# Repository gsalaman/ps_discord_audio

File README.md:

# Playstion/Discord Audio Mixer Project
This project provides a box that mixes together Audio and Microphone from both Playstation and Discord sources into a single headset. 

Quick Links:
* [Project Proposal](https://docs.google.com/document/d/1kymvg32hHtV9tEDY5p4hLi2L7wjIxDkjKmbJ4Tb4wR8/edit?usp=sharing)
* [Schedule](https://docs.google.com/spreadsheets/d/1bOIFvx7hpu0AlzfgVh9q8kjzmG0GHja3u-9B9gV9Qrc/edit?usp=sharing)
* [Journal](https://github.com/gsalaman/ps_discord_audio/blob/main/journal.md)
* [Design Document](https://docs.google.com/document/d/1ipFKIDMNCPuamUNVuetQo5jEzDj95vrXEs8RwQP3rsA/edit?usp=sharing)
* [Test Plan](https://docs.google.com/document/d/1uWEIeDPq-ZtmWTCWSF0HcOkNuqYgmgUuFNPxV6GTQaU/edit?usp=sharing)
* [Software Source (Arduino)](https://github.com/gsalaman/ps_discord_audio/tree/main/ghost_case_v1)
* [Hardware Source (Kicad & Gerber)](https://github.com/gsalaman/ps_discord_audio/tree/main/audio_quad_minimal)
* [User's Guide](https://docs.google.com/document/d/133C6y8KPKBfXd7hmt4fOLVRxKzTunB-pMatfn9UUioA/edit?usp=sharing)
* [Project Presentation](https://docs.google.com/presentation/d/1Z-V4jjkeFAulbqQNvLp17moSJGjj3tiSwEFrkb0hboE/edit?usp=sharing)

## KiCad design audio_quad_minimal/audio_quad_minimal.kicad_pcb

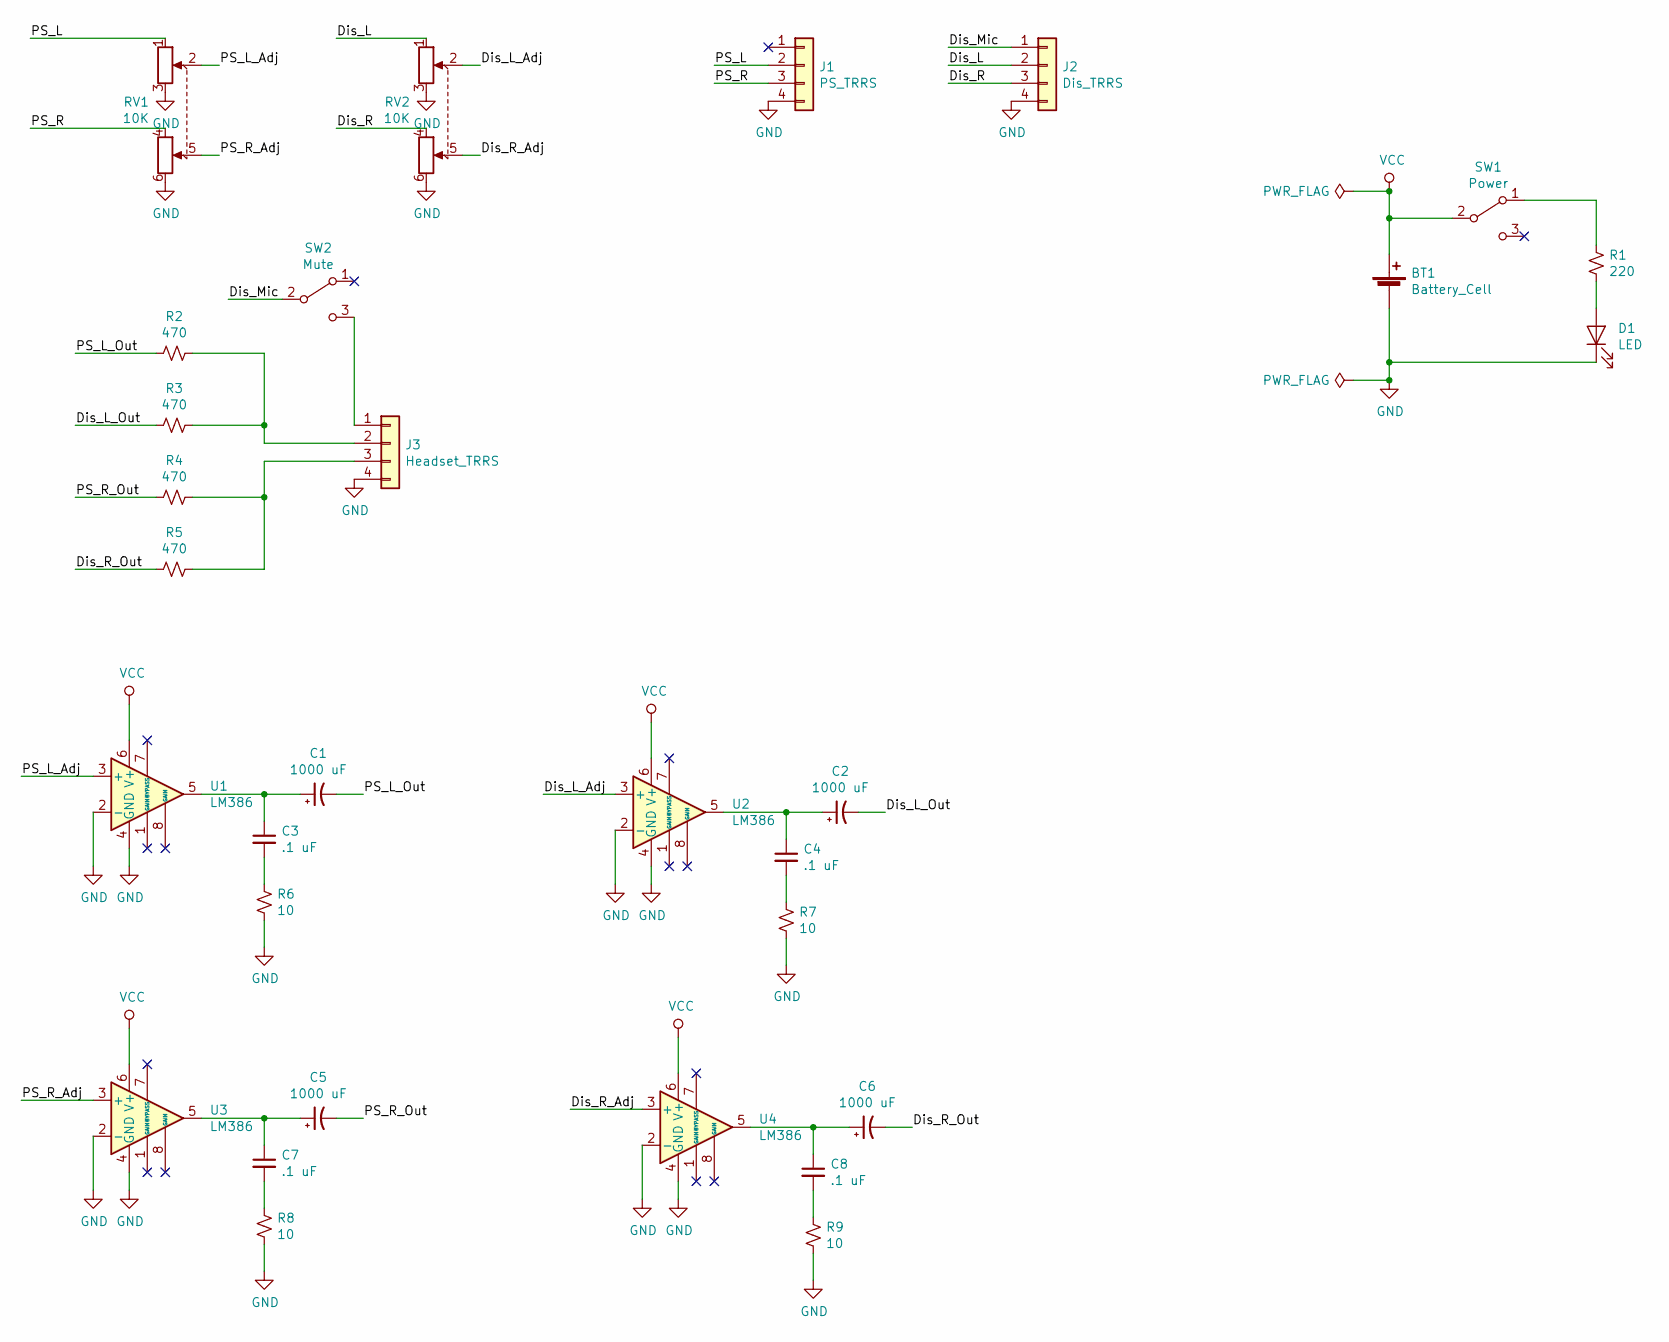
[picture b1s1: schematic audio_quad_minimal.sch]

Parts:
BT1: Battery_Cell; PinHeader_1x02_P2.54mm_Vertical
C1, C2, C5, C6: 1000 uF; CP_Elec_10x10
C3, C4, C7, C8: .1 uF; C_0603_1608Metric
D1: LED; LED_0805_2012Metric
J1: PS_TRRS; PinHeader_1x04_P2.54mm_Vertical
J2: Dis_TRRS; PinHeader_1x04_P2.54mm_Vertical
J3: Headset_TRRS; PinHeader_1x04_P2.54mm_Vertical
R1: 220; R_0603_1608Metric
R2, R3, R4, R5: 470; R_0603_1608Metric
R6, R7, R8, R9: 10; R_0603_1608Metric
RV1, RV2: 10K; PinHeader_2x03_P2.54mm_Vertical
SW1: Power; PinHeader_1x03_P2.54mm_Vertical
SW2: Mute; PinHeader_1x03_P2.54mm_Vertical
U1, U2, U3, U4: LM386; SOIC-8_3.9x4.9mm_P1.27mm

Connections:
/Dis_L: J2.2, RV2.1
/Dis_L_Adj: RV2.2, U2.3 (+)
/Dis_L_Out: C2.2, R3.2
/Dis_Mic: J2.1, SW2.2 (B)
/Dis_R: J2.3, RV2.4
/Dis_R_Adj: RV2.5, U4.3 (+)
/Dis_R_Out: C6.2, R5.2
/PS_L: J1.2, RV1.1
/PS_L_Adj: RV1.2, U1.3 (+)
/PS_L_Out: C1.2, R2.2
/PS_R: J1.3, RV1.4
/PS_R_Adj: RV1.5, U3.3 (+)
/PS_R_Out: C5.2, R4.2
GND: BT1.2 (-), D1.1 (K), J1.4, J2.4, J3.4, R6.2, R7.2, R8.2, R9.2, RV1.3, RV1.6, RV2.3, RV2.6, U1.2 (-), U1.4 (GND), U2.2 (-), U2.4 (GND), U3.2 (-), U3.4 (GND), U4.2 (-), U4.4 (GND)
unnamed: C1.1, C3.1, U1.5
unnamed: C2.1, C4.1, U2.5
unnamed: C3.2, R6.1
unnamed: C4.2, R7.1
unnamed: C5.1, C7.1, U3.5
unnamed: C6.1, C8.1, U4.5
unnamed: C7.2, R8.1
unnamed: C8.2, R9.1
unnamed: D1.2 (A), R1.2
unnamed: J3.1, SW2.3 (C)
unnamed: J3.2, R2.1, R3.1
unnamed: J3.3, R4.1, R5.1
unnamed: R1.1, SW1.1 (A)
VCC: BT1.1 (+), SW1.2 (B), U1.6 (V+), U2.6 (V+), U3.6 (V+), U4.6 (V+)

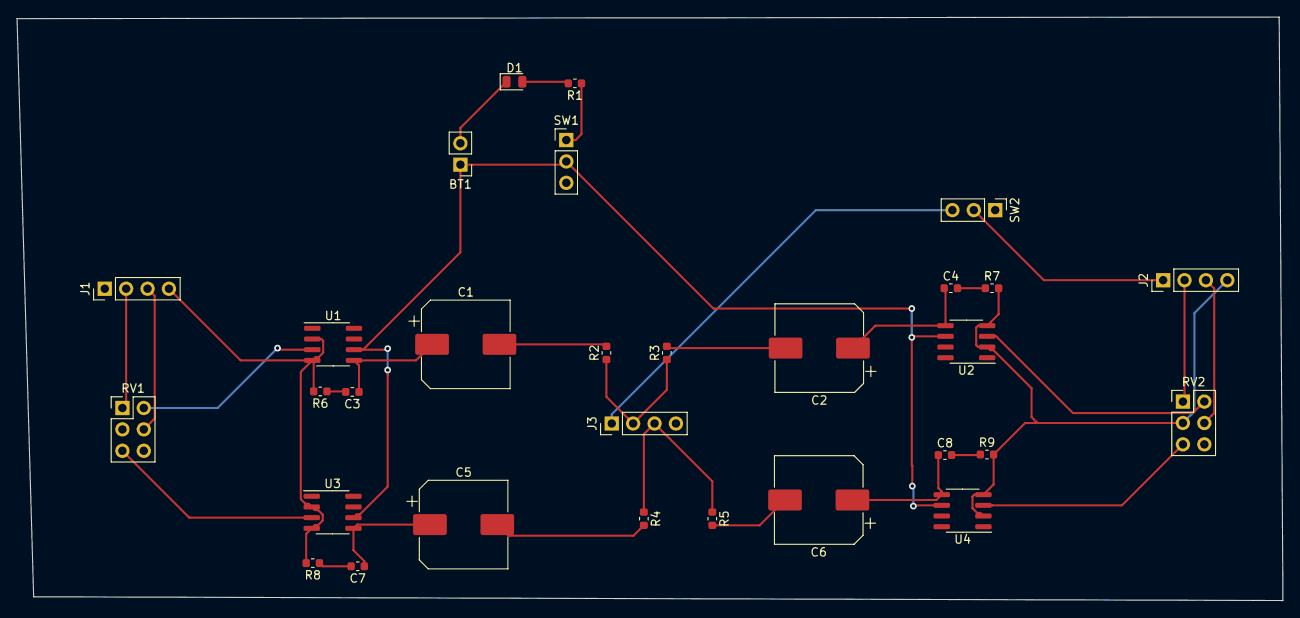
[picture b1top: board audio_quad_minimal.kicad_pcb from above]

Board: 2 copper layers, 150.3 x 69.3 mm, 30 parts (0 on the bottom side), 28 nets.

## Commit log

2021-07-28 Adding dir structure
2021-07-28 Adding Software and Hardware assets
2021-08-15 moving proposal
    Official link (referenced from the Readme) in google docs.
2021-08-15 migrating prototype doc to a journal
